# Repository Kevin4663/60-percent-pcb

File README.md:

# 60-percent-pcb
 Kevins 60% pcb design

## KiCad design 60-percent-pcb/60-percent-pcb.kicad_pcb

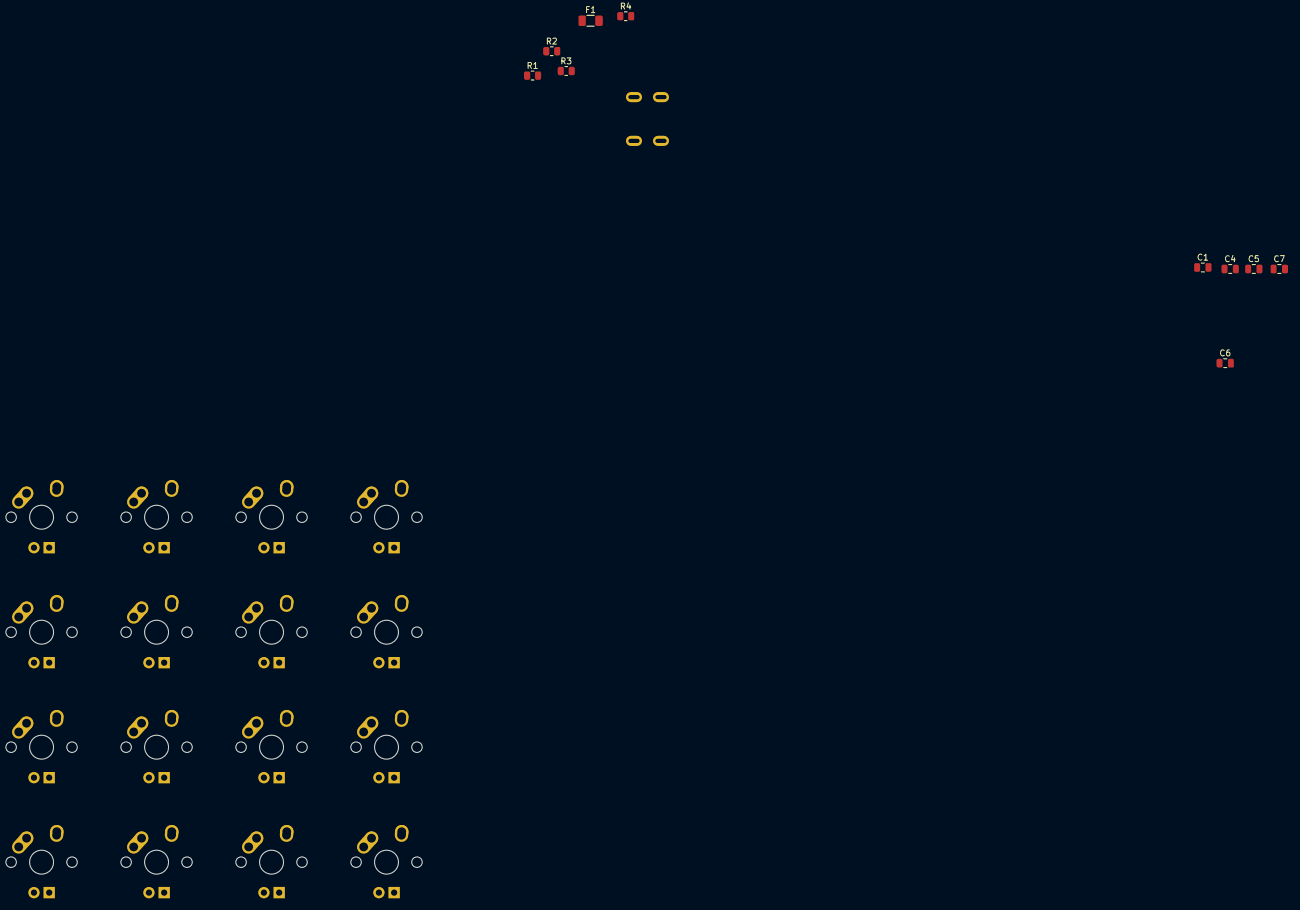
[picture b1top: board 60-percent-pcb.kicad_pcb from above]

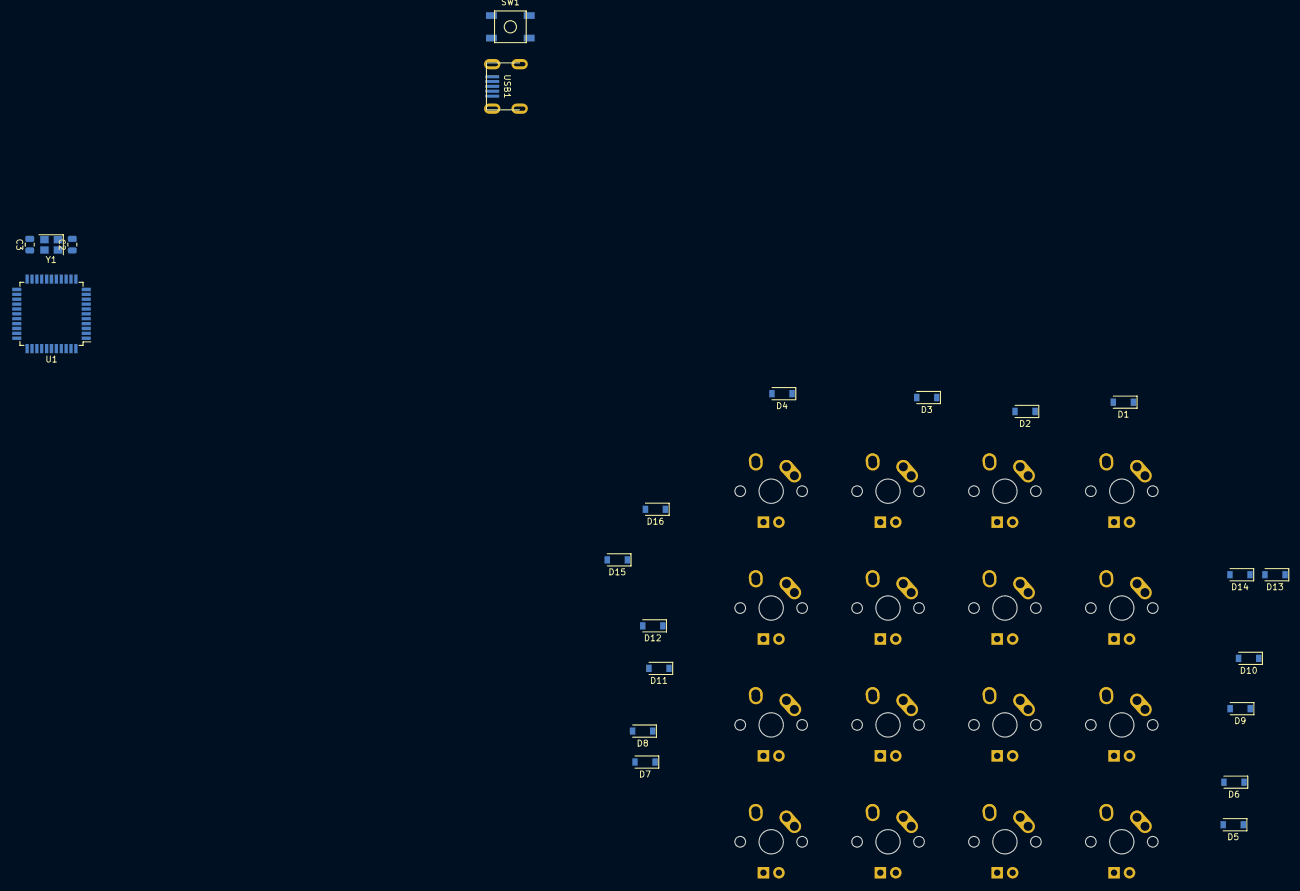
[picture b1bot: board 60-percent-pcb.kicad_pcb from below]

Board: 2 copper layers, 48 parts (22 on the bottom side), 36 nets, no tracks yet.

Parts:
C1, C4, C5: 0.1uF; C_0805_2012Metric
C2, C3: 22pF; C_0805_2012Metric
C6: 1uF; C_0805_2012Metric
C7: 10uF; C_0805_2012Metric
D1, D2, D3, D4, D5, D6, D7, D8, D9, D10, D11, D12, D13, D14, D15, D16: SOD-123; D_SOD-123
F1: 500mA; Fuse_1206_3216Metric
MX1, MX2, MX3, MX4, MX5, MX6, MX7, MX8, MX9, MX10, MX11, MX12, MX13, MX14, MX15, MX16: MX-NoLED; MX-1U
R1, R2: 22; R_0805_2012Metric
R3, R4: 10k; R_0805_2012Metric
SW1: SW_Push; SKQG-1155865
U1: ATmega32U4-AU; TQFP-44_10x10mm_P0.8mm
USB1: Molex-0548190589
Y1: Crystal_GND24_Small; Crystal_SMD_3225-4Pin_3.2x2.5mm

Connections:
+5V: C1.1, C4.1, C5.1, C7.1, F1.1, R3.1, U1.2, U1.7, U1.14, U1.24, U1.34, U1.44
COL0: MX1.1, MX2.1, MX3.1, MX4.1
COL1: MX5.1, MX6.1, MX7.1, MX8.1
COL2: MX9.1, MX10.1, MX11.1, MX12.1
COL3: MX13.1, MX14.1, MX15.1, MX16.1
D+: R2.2, USB1.2
D-: R1.1, USB1.4
GND: C1.2, C2.1, C3.2, C4.2, C5.2, C6.2, C7.2, R4.1, SW1.1, U1.5, U1.15, U1.23, U1.35, U1.43, USB1.1, Y1.2, Y1.4
unnamed: C2.2, U1.17, Y1.1
unnamed: C3.1, U1.16, Y1.3
unnamed: C6.1, U1.6
unnamed: D1.2, MX1.2
unnamed: D2.2, MX2.2
unnamed: D3.2, MX3.2
unnamed: D4.2, MX4.2
unnamed: D5.2, MX5.2
unnamed: D6.2, MX6.2
unnamed: D7.2, MX7.2
unnamed: D8.2, MX8.2
unnamed: D9.2, MX9.2
unnamed: D10.2, MX10.2
unnamed: D11.2, MX11.2
unnamed: D12.2, MX12.2
unnamed: D13.2, MX13.2
unnamed: D14.2, MX14.2
unnamed: D15.2, MX15.2
unnamed: D16.2, MX16.2
unnamed: R1.2, U1.3
unnamed: R2.1, U1.4
unnamed: R3.2, SW1.2, U1.13
unnamed: R4.2, U1.33
ROW0: D1.1, D5.1, D9.1, D13.1
ROW1: D2.1, D6.1, D10.1, D14.1
ROW2: D3.1, D7.1, D11.1, D15.1
ROW3: D4.1, D8.1, D12.1, D16.1
VCC: F1.2, USB1.5

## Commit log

2020-12-12 Add Submodules
2020-12-13 cool
